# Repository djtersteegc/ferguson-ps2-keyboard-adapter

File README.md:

PS/2 to parallel keyboard adapter designed to plug into the 26 pin header of a Ferguson Big Board Z80 SBC. Based on the work shared by [enrico](https://forum.vcfed.org/index.php?members/enrico.5315/) here, https://forum.vcfed.org/index.php?threads/ferguson-big-board-1-monitor-rom.32705/#post-405189

### BOM

https://djtersteegc.github.io/ferguson-ps2-keyboard-adapter/ibom.html

### Firmware Flashing

Available in the [firmware](firmware) directory.  Use your favorite Pic programmer like a Pickit3 with an adapter board or a TL866/T48.

### Revisions

#### v1.0

Tested and working

#### v1.1 (Current)

Add a 100nf decoupling cap for the Pic chip.

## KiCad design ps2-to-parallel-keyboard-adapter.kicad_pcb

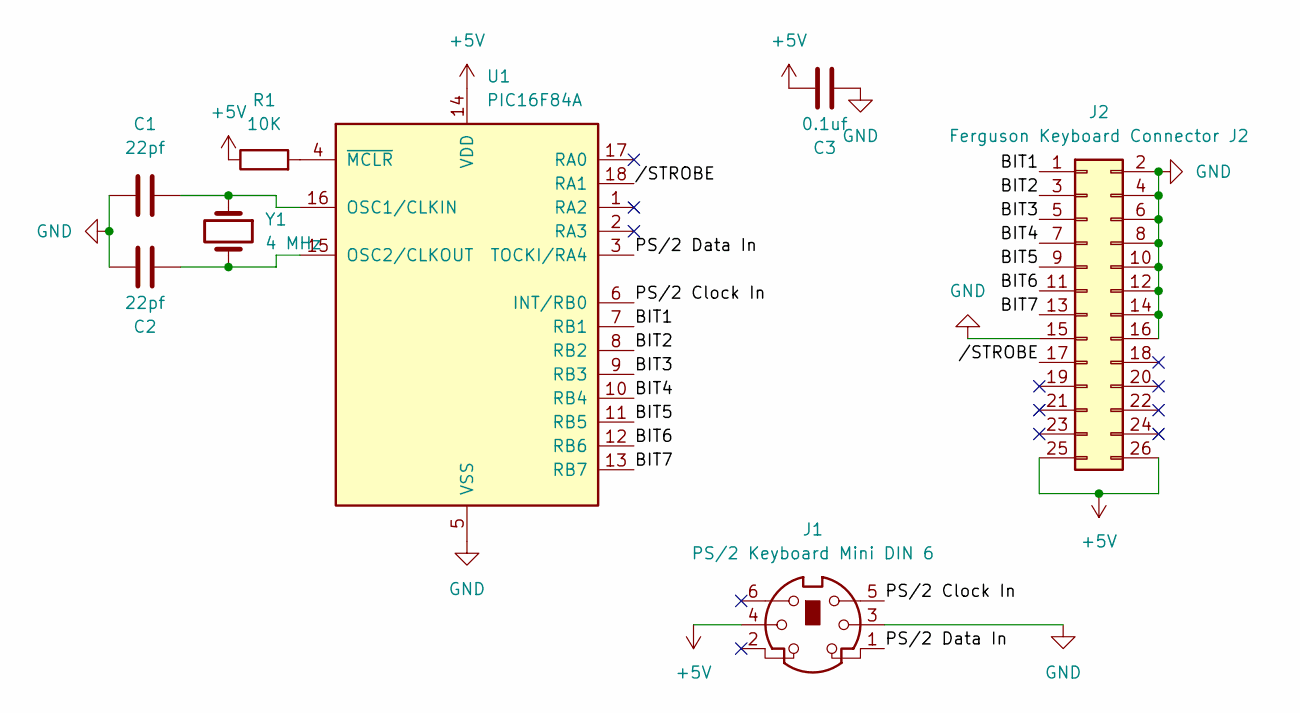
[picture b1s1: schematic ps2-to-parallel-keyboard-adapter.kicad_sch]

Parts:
C1, C2: 22pf; C_Rect_L4.0mm_W2.5mm_P2.50mm
C3: 0.1uf; C_Rect_L4.0mm_W2.5mm_P2.50mm
J1: PS/2 Keyboard Mini DIN 6; CUI_MD-60SM
J2: Ferguson Keyboard Connector J2; PinSocket_2x13_P2.54mm_Horizontal
R1: 10K; R_Axial_DIN0207_L6.3mm_D2.5mm_P7.62mm_Horizontal
U1: PIC16F84A; DIP-18_W7.62mm_Socket
Y1: 4 MHz; Crystal_HC49-U_Vertical

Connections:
+5V: C3.1, J1.4, J2.25, J2.26, R1.1, U1.14 (VDD)
/BIT1: J2.1, U1.7 (RB1)
/BIT2: J2.3, U1.8 (RB2)
/BIT3: J2.5, U1.9 (RB3)
/BIT4: J2.7, U1.10 (RB4)
/BIT5: J2.9, U1.11 (RB5)
/BIT6: J2.11, U1.12 (RB6)
/BIT7: J2.13, U1.13 (RB7)
/PS/2 Clock In: J1.5, U1.6 (INT/RB0)
/PS/2 Data In: J1.1, U1.3 (TOCKI/RA4)
//STROBE: J2.17, U1.18 (RA1)
GND: C1.1, C2.1, C3.2, J1.3, J2.2, J2.4, J2.6, J2.8, J2.10, J2.12, J2.14, J2.15, J2.16, U1.5 (VSS)
unnamed: C1.2, U1.16 (OSC1/CLKIN), Y1.1
unnamed: C2.2, U1.15 (OSC2/CLKOUT), Y1.2
unnamed: R1.2, U1.4 (~MCLR)

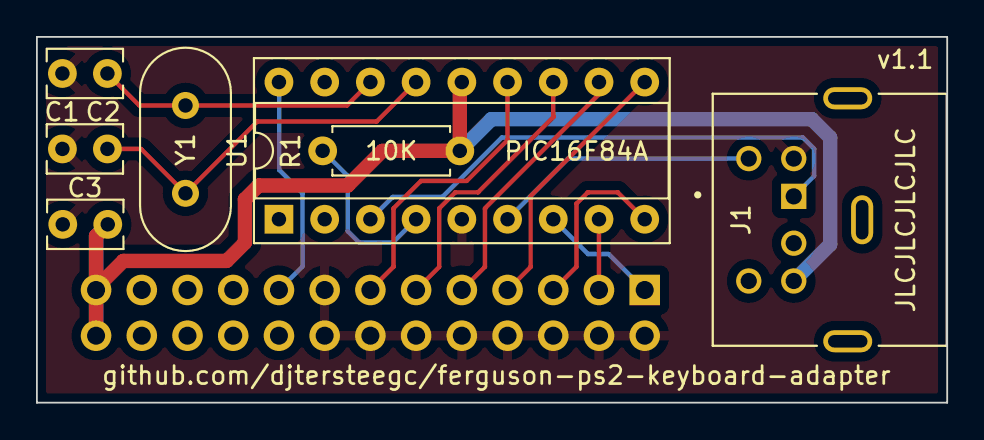
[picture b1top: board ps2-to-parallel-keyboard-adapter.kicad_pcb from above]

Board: 2 copper layers, 50.6 x 20.3 mm, 8 parts (1 on the bottom side), 15 nets.

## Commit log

2023-08-27 Initial Version
2025-01-07 v1.1, add decoupling cap
2025-01-07 Fix README image
